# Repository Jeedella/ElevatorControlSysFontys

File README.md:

# ElevatorControlSysFontys
This repository houses all relevant files of the Elevator Control System of Fontys Hogescholen Enginering

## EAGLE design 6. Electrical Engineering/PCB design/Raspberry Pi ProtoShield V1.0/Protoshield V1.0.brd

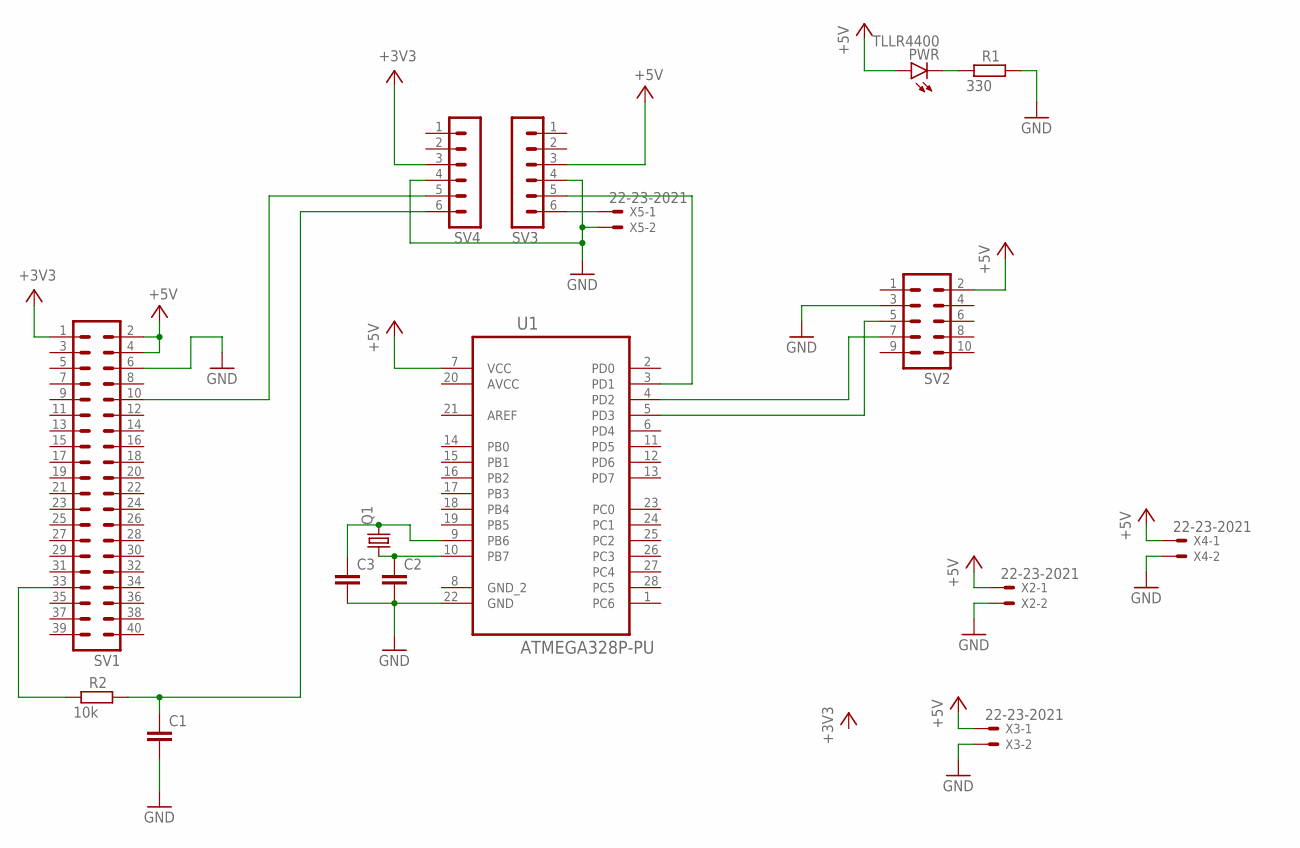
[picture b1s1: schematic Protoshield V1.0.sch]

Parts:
C1, C2, C3: C-EU050-024X044; C050-024X044
PWR: TLLR4400; LED3MM
Q1: CRYSTALHC49S; HC49/S
R1: 330; 0207/7
R2: 10k; 0207/7
SV1: MA20-2
SV2: MA05-2
SV3, SV4: MA06-1
U1: ATMEGA328P-PU; DIP254P762X457-28
X2, X3, X4, X5: 22-23-2021

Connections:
+3V3: SV1.1, SV4.3
+5V: PWR.A, SV1.2, SV1.4, SV2.2, SV3.3, U1.7 (VCC), X2.1, X3.1, X4.1
AVCC: U1.20 (AVCC)
GND: C1.2, C2.2, C3.2, R1.2, SV1.6, SV2.3, SV3.4, SV4.4, U1.22 (GND), X2.2, X3.2, X4.2, X5.2
unnamed: SV2.7, U1.4 (PD2)
unnamed: SV2.5, U1.5 (PD3)
unnamed: PWR.K (C), R1.1
unnamed: SV3.6, X5.1
unnamed: C3.1, Q1.2, U1.9 (PB6)
unnamed: C2.1, Q1.1, U1.10 (PB7)
unnamed: R2.1, SV1.33
unnamed: SV3.5, U1.3 (PD1)
unnamed: SV1.10, SV4.5
unnamed: C1.1, R2.2, SV4.6

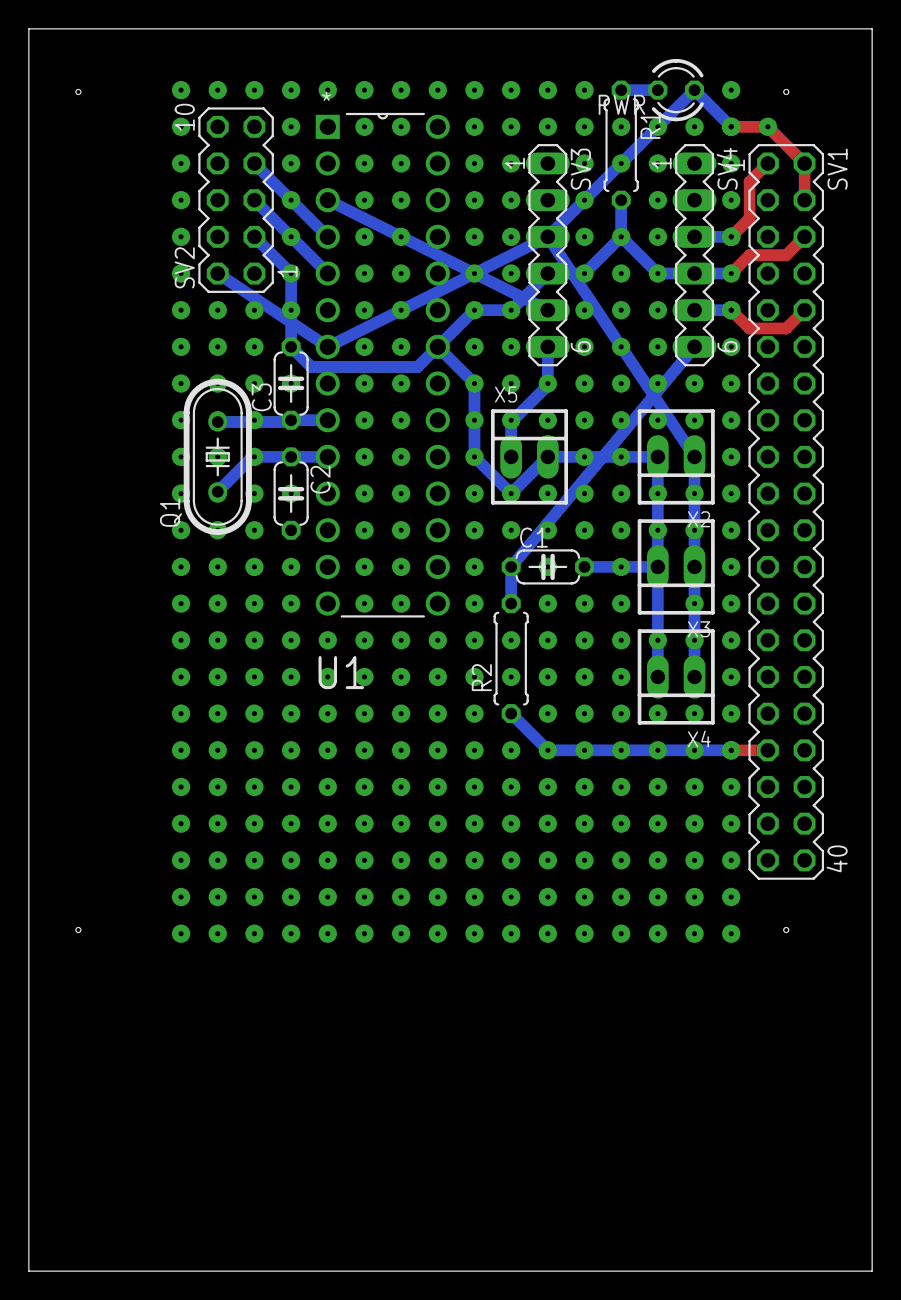
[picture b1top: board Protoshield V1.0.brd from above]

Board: 2 copper layers, 58.4 x 86.0 mm, 16 parts (0 on the bottom side), 13 nets.

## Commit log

2021-01-29 Created project structure and files
    Created folder structure
    Created Wiki
    Added System description
    Added PCB files
    Added Simulink files
2021-02-02 Added lots of documents
    Simulink files, updated documentation.
2021-02-07 First release of the project document
    Added hardware setup, software description, requirements and specifications.
2021-02-07 Added readme files for project structure
